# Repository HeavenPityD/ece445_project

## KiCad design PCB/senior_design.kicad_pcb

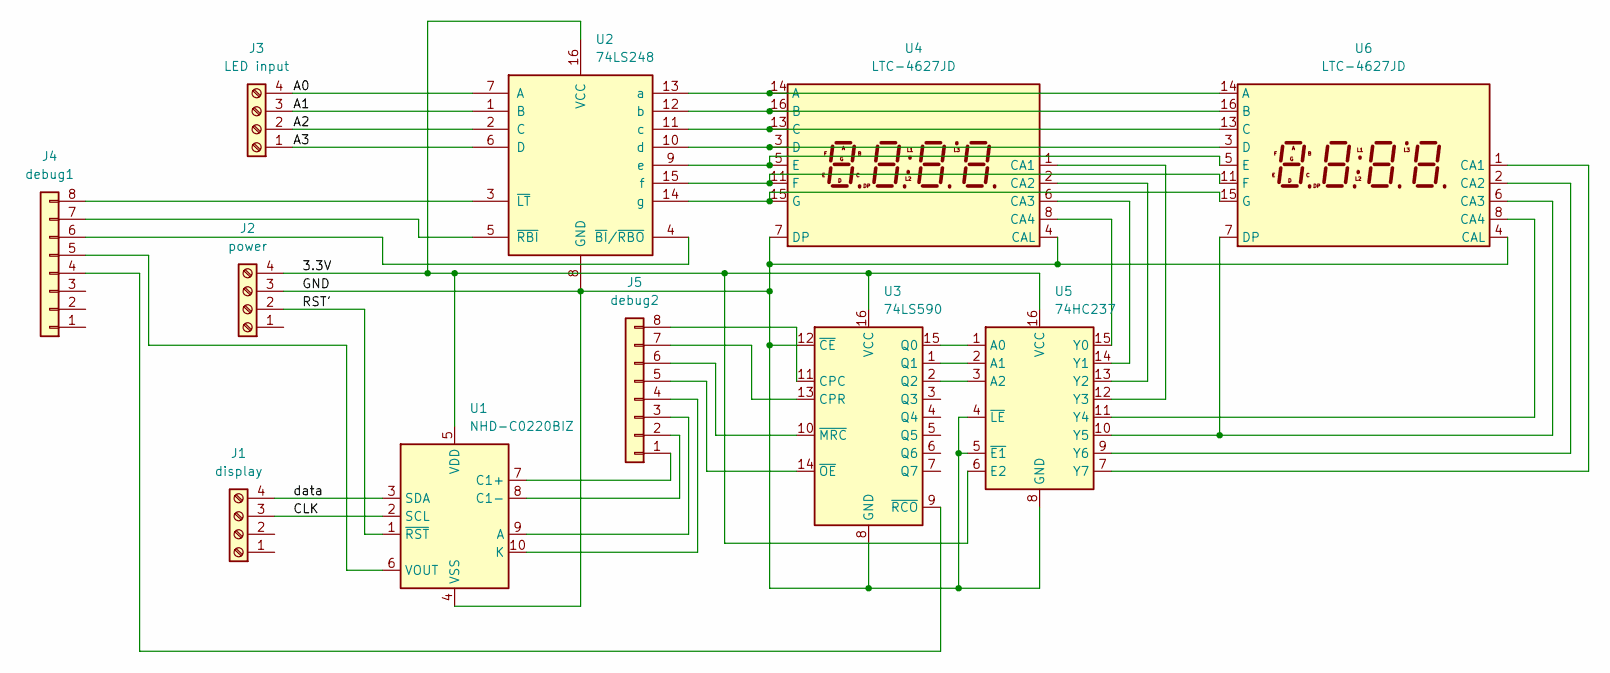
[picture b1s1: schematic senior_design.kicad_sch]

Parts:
J1: display; FanPinHeader_1x04_P2.54mm_Vertical
J2: power; FanPinHeader_1x04_P2.54mm_Vertical
J3: LED input; FanPinHeader_1x04_P2.54mm_Vertical
J4: debug1; PinHeader_1x08_P2.54mm_Horizontal
J5: debug2; PinHeader_1x08_P2.54mm_Horizontal
U1: NHD-C0220BIZ; NHD-C0220BiZ
U2: 74LS248; Decoder_74LS248
U3: 74LS590; Counter_74LS590
U4, U6: LTC-4627JD; LTC-4627Jx
U5: 74HC237; Demult_CD74HC237

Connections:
/3.3V: J2.4, U1.5 (VDD), U2.16 (VCC), U3.16 (VCC), U5.6 (E2), U5.16 (VCC)
/A0: J3.4, U2.7 (A)
/A1: J3.3, U2.1 (B)
/A2: J3.2, U2.2 (C)
/A3: J3.1, U2.6 (D)
/CLK: J1.3, U1.2 (SCL)
/GND: J2.3, U1.4 (VSS), U2.8 (GND), U3.8 (GND), U3.12 (~CE), U4.4 (CAL), U4.7 (DP), U5.4 (~LE), U5.5 (~E1), U5.8 (GND), U6.4 (CAL)
/RST': J2.2, U1.1 (~RST)
/data: J1.4, U1.3 (SDA)
unnamed: J4.5, U1.6 (VOUT)
unnamed: J5.1, U1.7 (C1+)
unnamed: J5.2, U1.8 (C1-)
unnamed: J5.3, U1.9 (A)
unnamed: J5.4, U1.10 (K)
unnamed: J4.8, U2.3 (~LT)
unnamed: J4.6, U2.4 (~BI/~RBO)
unnamed: J4.7, U2.5 (~RBI)
unnamed: U2.9 (e), U4.5 (E), U6.5 (E)
unnamed: U2.10 (d), U4.3 (D), U6.3 (D)
unnamed: U2.11 (c), U4.13 (C), U6.13 (C)
unnamed: U2.12 (b), U4.16 (B), U6.16 (B)
unnamed: U2.13 (a), U4.14 (A), U6.14 (A)
unnamed: U2.14 (g), U4.15 (G), U6.15 (G)
unnamed: U2.15 (f), U4.11 (F), U6.11 (F)
unnamed: U3.1 (Q1), U5.2 (A1)
unnamed: U3.2 (Q2), U5.3 (A2)
unnamed: J4.4, U3.9 (~RCO)
unnamed: J5.6, U3.10 (~MRC)
unnamed: J5.8, U3.11 (CPC)
unnamed: J5.7, U3.13 (CPR)
unnamed: J5.5, U3.14 (~OE)
unnamed: U3.15 (Q0), U5.1 (A0)
unnamed: U4.1 (CA1), U5.12 (Y3)
unnamed: U4.2 (CA2), U5.13 (Y2)
unnamed: U4.6 (CA3), U5.14 (Y1)
unnamed: U4.8 (CA4), U5.15 (Y0)
unnamed: U5.7 (Y7), U6.1 (CA1)
unnamed: U5.9 (Y6), U6.2 (CA2)
unnamed: U5.10 (Y5), U6.6 (CA3), U6.7 (DP)
unnamed: U5.11 (Y4), U6.8 (CA4)

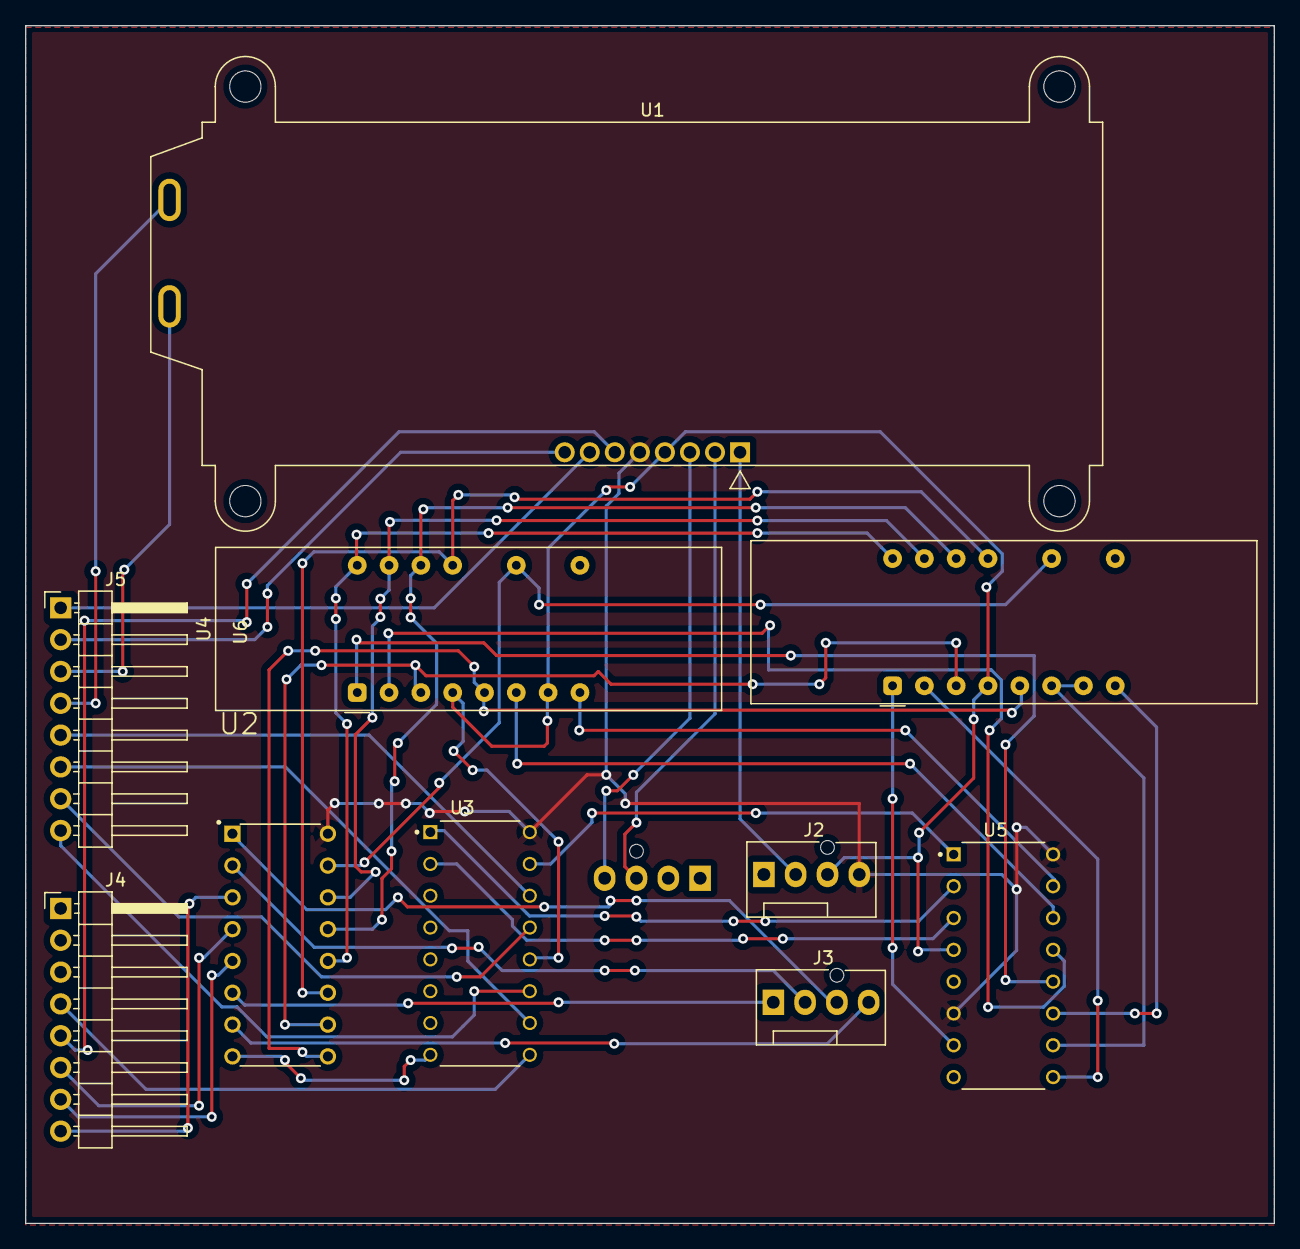
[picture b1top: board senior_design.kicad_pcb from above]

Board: 2 copper layers, 99.7 x 95.6 mm, 11 parts (1 on the bottom side), 40 nets.

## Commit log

2022-10-27 orderbook
2022-11-01 add PCB files
2022-11-07 new release
2022-11-07 remove vscode folder
2022-11-07 move files to root directory
2022-11-08 remove irrelevant files
2022-11-17 add strategy.cpp
2022-11-17 remove strategy
2022-11-17 remove readme
2022-11-17 add FPGA files
2022-11-23 add display driver
2022-11-23 add project file
2022-11-27 test i2c controller
2022-11-27 hardcode message
2022-11-27 led driver testbecnh
2022-11-28 LED completed
2022-11-29 connect different parts
